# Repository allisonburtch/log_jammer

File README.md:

Hi there. I found [this](http://www.electroschematics.com/wp-content/uploads/2009/01/cell-phone-jammer-schematic.gif) cell phone jammer on the internet. It is for the GSM 1900 spectrum. Many of these parts are legacy and I had to figure out replacements. If you look at the actual schematic in Eagle, I've noted the new name of each part. Feel free to email me with questions: allison//at//allisonburtch.net

Schematic in Eagle of triangle wave generator, voltage inverter and noise generator.

Schematic of the VCO and rf amplifier leading to antenna.

This is the board layout of the rf part in Eagle.

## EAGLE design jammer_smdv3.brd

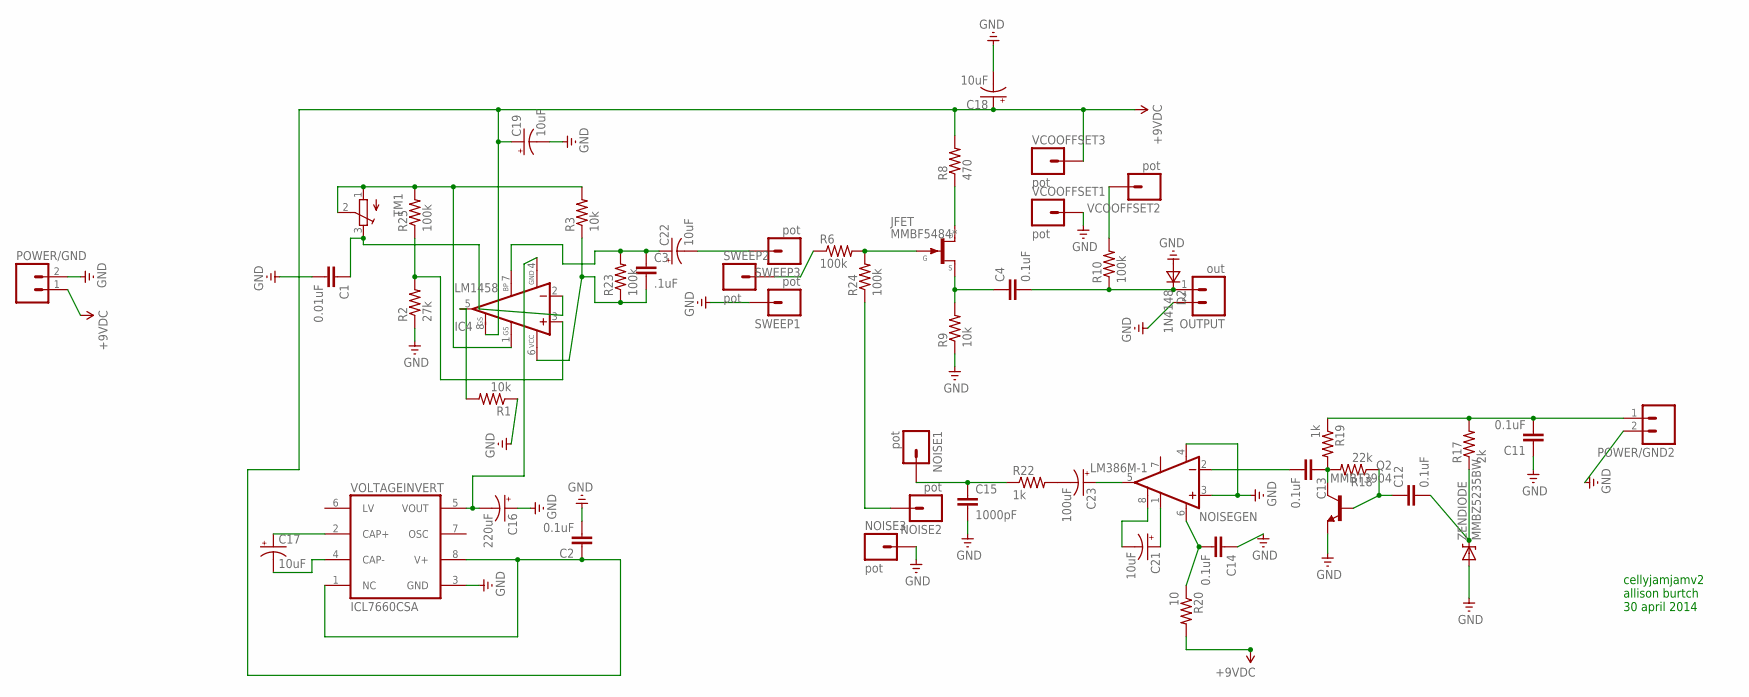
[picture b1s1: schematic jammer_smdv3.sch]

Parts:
C1: 0.01uF; 0603-CAP
C2, C4, C11, C12, C13, C14: 0.1uF; 0603-CAP
C3: .1uF; 0603-CAP
C15: 1000pF; 0603-CAP
C16: 220uF; PANASONIC_D
C17, C22: 10uF; PANASONIC_C
C18, C19, C21: 10uF; EIA3216
C23: 100uF; CPOL-RADIAL-100UF-25V
D2: 1N4148; SOD323
IC4: LM1458; SO08@2
JFET: MMBF5484*; SOT23
NOISE1, NOISE2, NOISE3: pot; 1X01
NOISEGEN: LM386M-1; SO08
OUTPUT: out; 1X02_LOCK_LONGPADS
POWER/GND, POWER/GND2: M02LOCK_LONGPADS; 1X02_LOCK_LONGPADS
Q2: MMBT3904; SOT23-BEC
R1, R3, R9: 10k; 0603-RES
R2: 27k; 0603-RES
R6, R10, R23, R24, R25: 100k; 0603-RES
R8: 470; 0603-RES
R17: 2k; 0603-RES
R18: 22k; 0603-RES
R19, R22: 1k; 0603-RES
R20: 10; 0603-RES
SWEEP1, SWEEP2, SWEEP3: pot; 1X01
TM1: TRIMPOTTC33X; TC33X
VCOOFFSET1, VCOOFFSET2, VCOOFFSET3: pot; 1X01
VOLTAGEINVERT: ICL7660CSA; SO08
ZENDIODE: MMBZ5235BW; DIODE-ZENER

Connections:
GND: C1.2, C2.2, C11.1, C14.1, C15.2, C16.+, C18.C (-), C19.C (-), D2.2 (A), NOISE3.1, NOISEGEN.3 (+IN), NOISEGEN.4 (GND), OUTPUT.2, POWER/GND.2, POWER/GND2.2, Q2.E, R1.1, R2.1, R9.1, SWEEP1.1, VCOOFFSET1.1, VOLTAGEINVERT.3 (GND), ZENDIODE.P$2 (A)
unnamed: C17.+, VOLTAGEINVERT.2 (CAP+)
unnamed: C17.-, VOLTAGEINVERT.4 (CAP-)
unnamed: C21.A (+), NOISEGEN.1 (GAIN)
unnamed: C16.-, IC4.4 (GND), VOLTAGEINVERT.5 (VOUT)
unnamed: IC4.1 (GAIN), R3.2, R25.2, TM1.1 (A), TM1.2 (S)
unnamed: C1.1, IC4.2 (-IN), TM1.3 (E)
unnamed: R6.1, SWEEP2.1
unnamed: C22.-, SWEEP3.1
unnamed: C3.2, IC4.6 (VS), R3.1, R23.1
unnamed: C21.C (-), NOISEGEN.8 (GAIN)
unnamed: C12.1, Q2.B, R18.1
unnamed: C13.2, NOISEGEN.2 (-IN)
unnamed: C13.1, Q2.C, R18.2, R19.2
unnamed: C12.2, R17.1, ZENDIODE.P$1 (C)
unnamed: C23.2 (-), R22.2
unnamed: C23.1 (+), NOISEGEN.5 (OUT)
unnamed: C15.1, NOISE1.1, R22.1
unnamed: C3.1, C22.+, IC4.7 (BS2), R23.2
unnamed: NOISE2.1, R24.1
unnamed: C14.2, NOISEGEN.6 (VS), R20.1
unnamed: JFET.1 (D), R8.1
unnamed: C4.1, JFET.2 (S), R9.2
unnamed: R10.2, VCOOFFSET2.1
unnamed: C11.2, POWER/GND2.1, R17.2, R19.1
unnamed: JFET.3 (G), R6.2, R24.2
unnamed: IC4.5 (OUT), R1.2
unnamed: IC4.3 (+IN), R2.2, R25.1
unnamed: C4.2, D2.1 (C), OUTPUT.1, R10.1
VCC: C2.1, C18.A (+), C19.A (+), IC4.8 (GAIN), POWER/GND.1, R8.2, R20.2, VCOOFFSET3.1, VOLTAGEINVERT.1 (NC), VOLTAGEINVERT.8 (V+)

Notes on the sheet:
cellyjamjamv2 allison burtch 30 april 2014

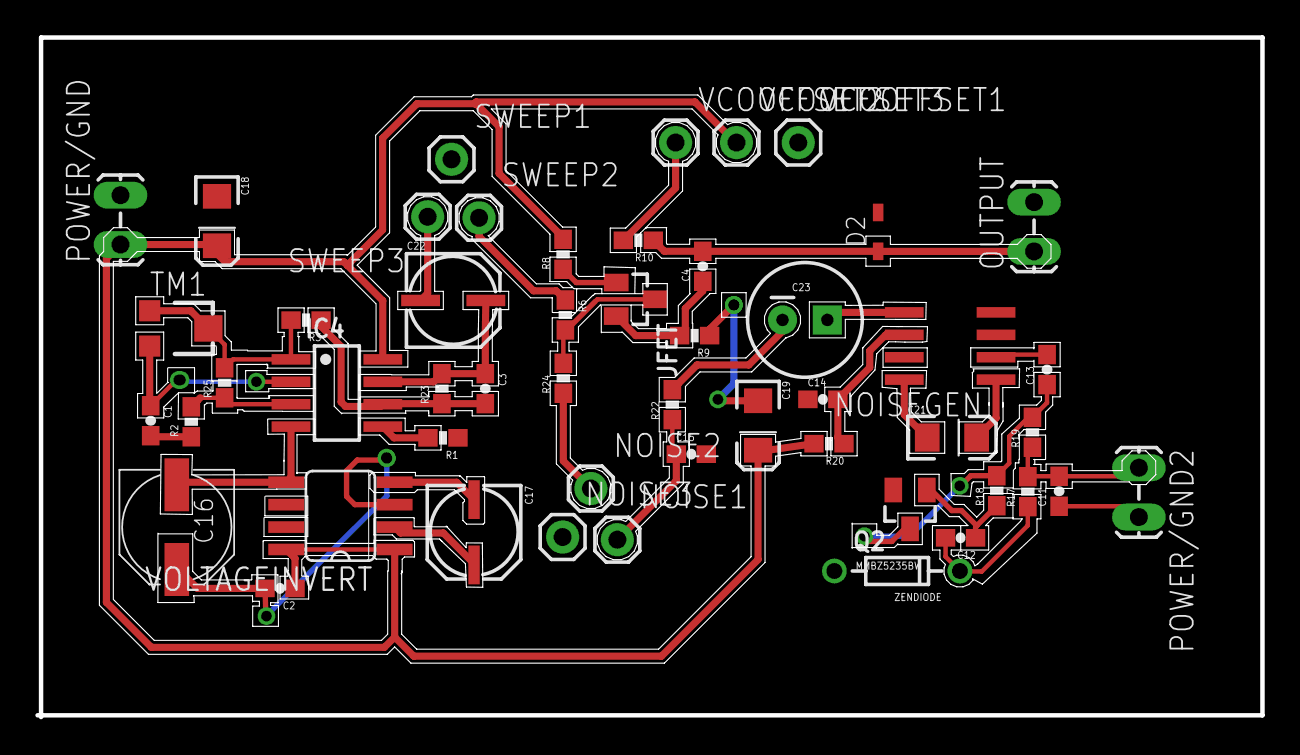
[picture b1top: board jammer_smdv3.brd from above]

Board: 2 copper layers, 69.4 x 38.5 mm, 51 parts (0 on the bottom side), 30 nets.

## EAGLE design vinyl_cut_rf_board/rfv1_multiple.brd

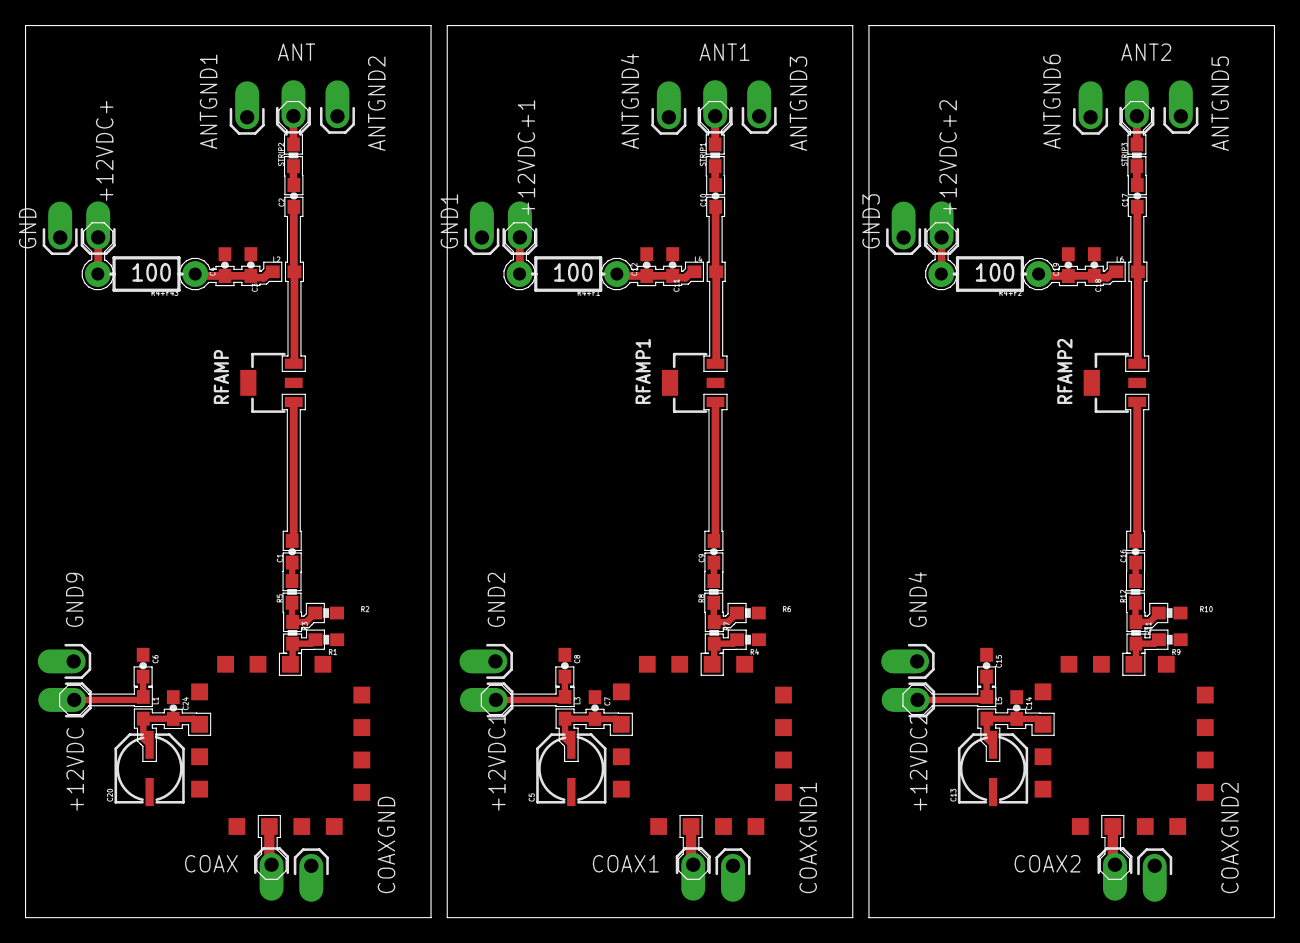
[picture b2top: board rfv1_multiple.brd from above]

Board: 2 copper layers, 97.8 x 69.8 mm, 78 parts (0 on the bottom side), 39 nets.

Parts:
+12VDC, +12VDC1, +12VDC2, +12VDC+, +12VDC+1, +12VDC+2: 1X01_OFFSET
ANT, ANT1, ANT2: 1X01_OFFSET
ANTGND1, ANTGND2, ANTGND3, ANTGND4, ANTGND5, ANTGND6: 1X01_OFFSET
C1, C2, C3, C9, C10, C11, C16, C17, C18: 68pF; 0603-CAP
C4, C12, C19: 0.01uF; 0603-CAP
C5, C13, C20: 10uF; PANASONIC_C
C6, C7, C8, C14, C15, C24: 0.1uF; 0603-CAP
COAX, COAX1, COAX2: 1X01_OFFSET
COAXGND, COAXGND1, COAXGND2: GND; 1X01_OFFSET
GND, GND1, GND2, GND3, GND4, GND9: 1X01_OFFSET
L1, L3, L5: 10uh; 0603
L2, L4, L6: 27nH; 0603
R1, R2, R4, R6, R9, R10: 220; 0603-RES
R3, R7, R11: 24; 0603-RES
R4+F1, R4+F2, R4+F43: 100; AXIAL-0.3-KIT
R5, R8, R12: strip1; 0603-RES
RFAMP, RFAMP1, RFAMP2: AG603-89; SOT89
STRIP1, STRIP2, STRIP3: strip1; 0603-RES
U$1, U$2, U$3: CVCO55CL

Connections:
GND: ANTGND1.1, ANTGND2.1, C3.2, C4.2, C6.1, C20.-, C24.1, COAXGND.1, GND.1, GND9.1, R1.1, R2.1, RFAMP.2, RFAMP.4, U$1.P$1, U$1.P$3, U$1.P$4, U$1.P$5, U$1.P$6, U$1.P$7, U$1.P$8, U$1.P$9, U$1.P$11, U$1.P$12, U$1.P$13, U$1.P$15, U$1.P$16
GND1: ANTGND3.1, ANTGND4.1, C5.-, C7.1, C8.1, C11.2, C12.2, COAXGND1.1, GND1.1, GND2.1, R4.1, R6.1, RFAMP1.2, RFAMP1.4, U$2.P$1, U$2.P$3, U$2.P$4, U$2.P$5, U$2.P$6, U$2.P$7, U$2.P$8, U$2.P$9, U$2.P$11, U$2.P$12, U$2.P$13, U$2.P$15, U$2.P$16
GND2: ANTGND5.1, ANTGND6.1, C13.-, C14.1, C15.1, C18.2, C19.2, COAXGND2.1, GND3.1, GND4.1, R9.1, R10.1, RFAMP2.2, RFAMP2.4, U$3.P$1, U$3.P$3, U$3.P$4, U$3.P$5, U$3.P$6, U$3.P$7, U$3.P$8, U$3.P$9, U$3.P$11, U$3.P$12, U$3.P$13, U$3.P$15, U$3.P$16
unnamed: COAX.1, U$1.P$2
unnamed: R1.2, R3.2, U$1.P$10
unnamed: R2.2, R3.1, R5.1
unnamed: C1.2, RFAMP.1
unnamed: C2.1, L2.2, RFAMP.3
unnamed: C3.1, C4.1, L2.1, R4+F43.P$1
unnamed: +12VDC.1, C6.2, L1.1
unnamed: +12VDC+.1, R4+F43.P$2
unnamed: C2.2, STRIP2.1
unnamed: ANT.1, STRIP2.2
unnamed: C1.1, R5.2
unnamed: C5.+, C7.2, L3.2, U$2.P$14
unnamed: COAX1.1, U$2.P$2
unnamed: R4.2, R7.2, U$2.P$10
unnamed: R6.2, R7.1, R8.1
unnamed: C9.2, RFAMP1.1
unnamed: C10.1, L4.2, RFAMP1.3
unnamed: C11.1, C12.1, L4.1, R4+F1.P$1
unnamed: +12VDC1.1, C8.2, L3.1
unnamed: +12VDC+1.1, R4+F1.P$2
unnamed: C10.2, STRIP1.1
unnamed: ANT1.1, STRIP1.2
unnamed: C9.1, R8.2
unnamed: C13.+, C14.2, L5.2, U$3.P$14
unnamed: COAX2.1, U$3.P$2
unnamed: R9.2, R11.2, U$3.P$10
unnamed: R10.2, R11.1, R12.1
unnamed: C16.2, RFAMP2.1
unnamed: C17.1, L6.2, RFAMP2.3
unnamed: C18.1, C19.1, L6.1, R4+F2.P$1
unnamed: +12VDC2.1, C15.2, L5.1
unnamed: +12VDC+2.1, R4+F2.P$2
unnamed: C17.2, STRIP3.1
unnamed: ANT2.1, STRIP3.2
unnamed: C16.1, R12.2
unnamed: C20.+, C24.2, L1.2, U$1.P$14

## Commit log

2014-03-11 added readme
2014-03-11 finished schematic, now onto board. jeeez
2014-03-11 added gitignore
2014-03-11 removed cached changes
2014-03-14 design is better
2014-03-17 added correct VCO
2014-03-24 added VCO, changed design. still needs a lot of work
2014-04-20 changed everything to SMD. much work to be done
2014-04-30 surface mount board
2014-04-30 designin'
2014-05-01 fuuuuuuu had to hand draw the ulp
2014-05-02 mill file traces were too close. redrew them.
2014-05-02 changed board
2014-05-03 third version of design
2014-10-21 updated github with rf board and vinyl stencil
2014-10-21 added screenshots
2014-10-21 images
2014-10-21 updated gitignore
2014-10-21 rm extra files

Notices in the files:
parts and their libraries:
SparkFun-Resistors: Licensing: CC v3.0 Share-Alike You are welcome to use this library for commercial purposes.
supply0: Copyright (C) 2007, Bob Starr
mini-circuits: Copyright (C) 2013, Bob Starr
